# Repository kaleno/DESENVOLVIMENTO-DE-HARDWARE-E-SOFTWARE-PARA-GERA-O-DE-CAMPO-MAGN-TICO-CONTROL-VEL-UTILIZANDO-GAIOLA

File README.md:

# DESENVOLVIMENTO DE HARDWARE E SOFTWARE PARA GERAÇÃO DE CAMPO MAGNÉTICO CONTROLÁVEL

Este repositório contém o trabalho de desenvolvimento de hardware e software realizado no âmbito do Laboratório de Controle e Simulação de Sistemas Aeroespaciais (LODESTAR) da Universidade de Brasília (UnB). O objetivo principal é criar uma plataforma com interface gráfica para a geração de campo magnético controlável, direcionada para aplicações no simulador de pequenos satélites do LODESTAR.

## Visão Geral

O sistema atual do laboratório inclui uma gaiola de Helmholtz com dois pares de bobinas por eixo, uma estação de trabalho e fontes de tensão controláveis. Este projeto propõe atualizações e o desenvolvimento de novas funcionalidades para a plataforma existente.

Algumas das aplicações planejadas são:

- Reprodução do campo magnético em malha fechada utilizando o modelo International Geomagnetic Reference Field (IGRF) em conjunto com o propagador de órbita Simplified General Perturbations (SGP4).
- Reprodução dos vetores de campo magnético coletados pelos sensores do satélite AlfaCrux, recentemente lançado.
- Realização de testes preliminares para validar o novo sistema no contexto dos projetos em andamento no LODESTAR.

## Estrutura do Repositório

O repositório está organizado da seguinte forma:

- `Firmware_Circuito_Inversor/`: Contém os arquivos relacionados ao firmware do circuito inversor.
- `Outros/`: Diretório para outros arquivos relevantes.
- `PonteH/`: Contém os arquivos relacionados à ponte H.
- `PonteH2.0/`: Contém os arquivos relacionados à versão 2.0 da ponte H.
- `Software_Gaiola/`: Contém os arquivos relacionados ao software da gaiola de Helmholtz.
- `Manual_Gaiola_de_Helmholtz_(1).pdf`: Documento PDF contendo o manual da gaiola de Helmholtz.
- `README.md`: Este arquivo README com informações sobre o projeto.
- `TCC_ThiagoHenriqueFerreiradaSilva_biblioteca.pdf`: Documento PDF contendo o TCC (Trabalho de Conclusão de Curso) intitulado "DESENVOLVIMENTO DE HARDWARE E SOFTWARE PARA GERAÇÃO DE CAMPO MAGNÉTICO CONTROLÁVEL".

Certifique-se de ajustar os nomes dos diretórios e arquivos de acordo com a estrutura do seu repositório.

## Pré-requisitos e Instalação

1. Certifique-se de ter os seguintes componentes presentes no arquivo requirements.bat

2. Clone este repositório em sua máquina local usando o seguinte comando:

**git clone https://github.com/seu-usuario/nome-do-repositorio.git**

3. Navegue até o diretório clonado.

4. Siga as instruções específicas contidas em `Manual_Gaiola_de_Helmholtz_(1).pdf` para configurar e instalar as respectivas partes do sistema.

## Utilização

1. Certifique-se de que o hardware está corretamente configurado e conectado à sua estação de trabalho.

2. Inicie o software e abra a interface gráfica do sistema.

3. Utilize as funcionalidades disponíveis para gerar o campo magnético controlável de acordo com suas necessidades.

4. Consulte a documentação disponível em `docs/` para obter informações adicionais sobre a utilização do sistema.

## Contribuição

Se você deseja contribuir para este projeto, sinta-se à vontade para enviar um pull request com suas melhorias. Toda contribuição é bem-vinda!

## Licença

Este projeto é licenciado sob a MIT. Consulte o arquivo LICENSE para obter mais informações.

## Contato

Para mais informações sobre este projeto, entre em contato conosco:

- Nome: Thiago Henrique Ferreira da Silva
- E-mail: thiago.henriquef@hotmail.com

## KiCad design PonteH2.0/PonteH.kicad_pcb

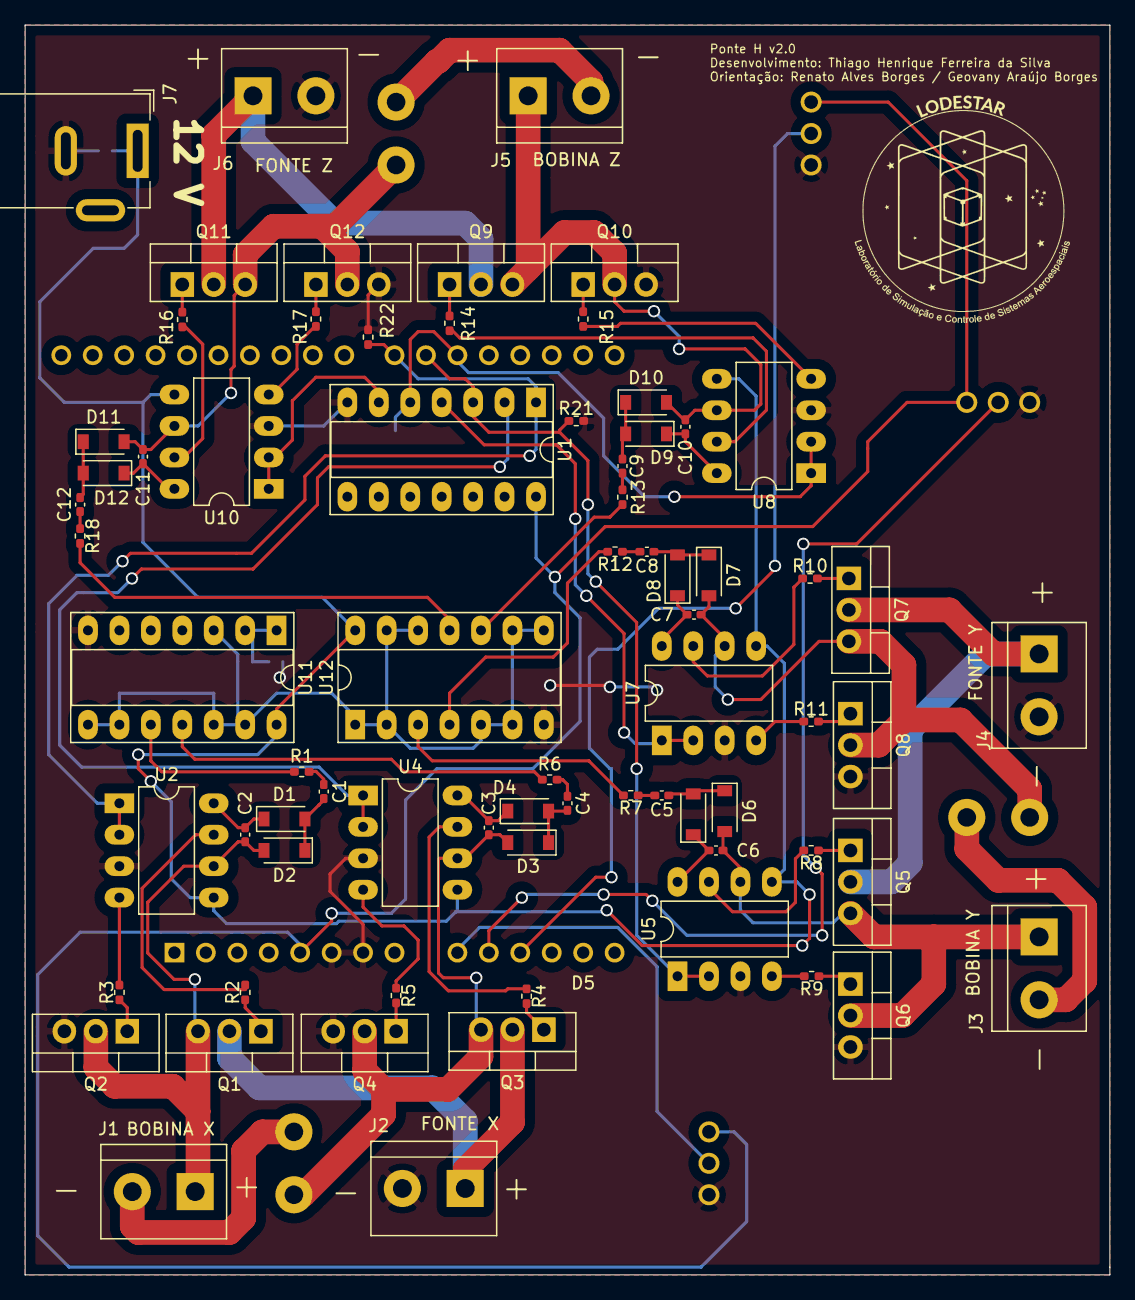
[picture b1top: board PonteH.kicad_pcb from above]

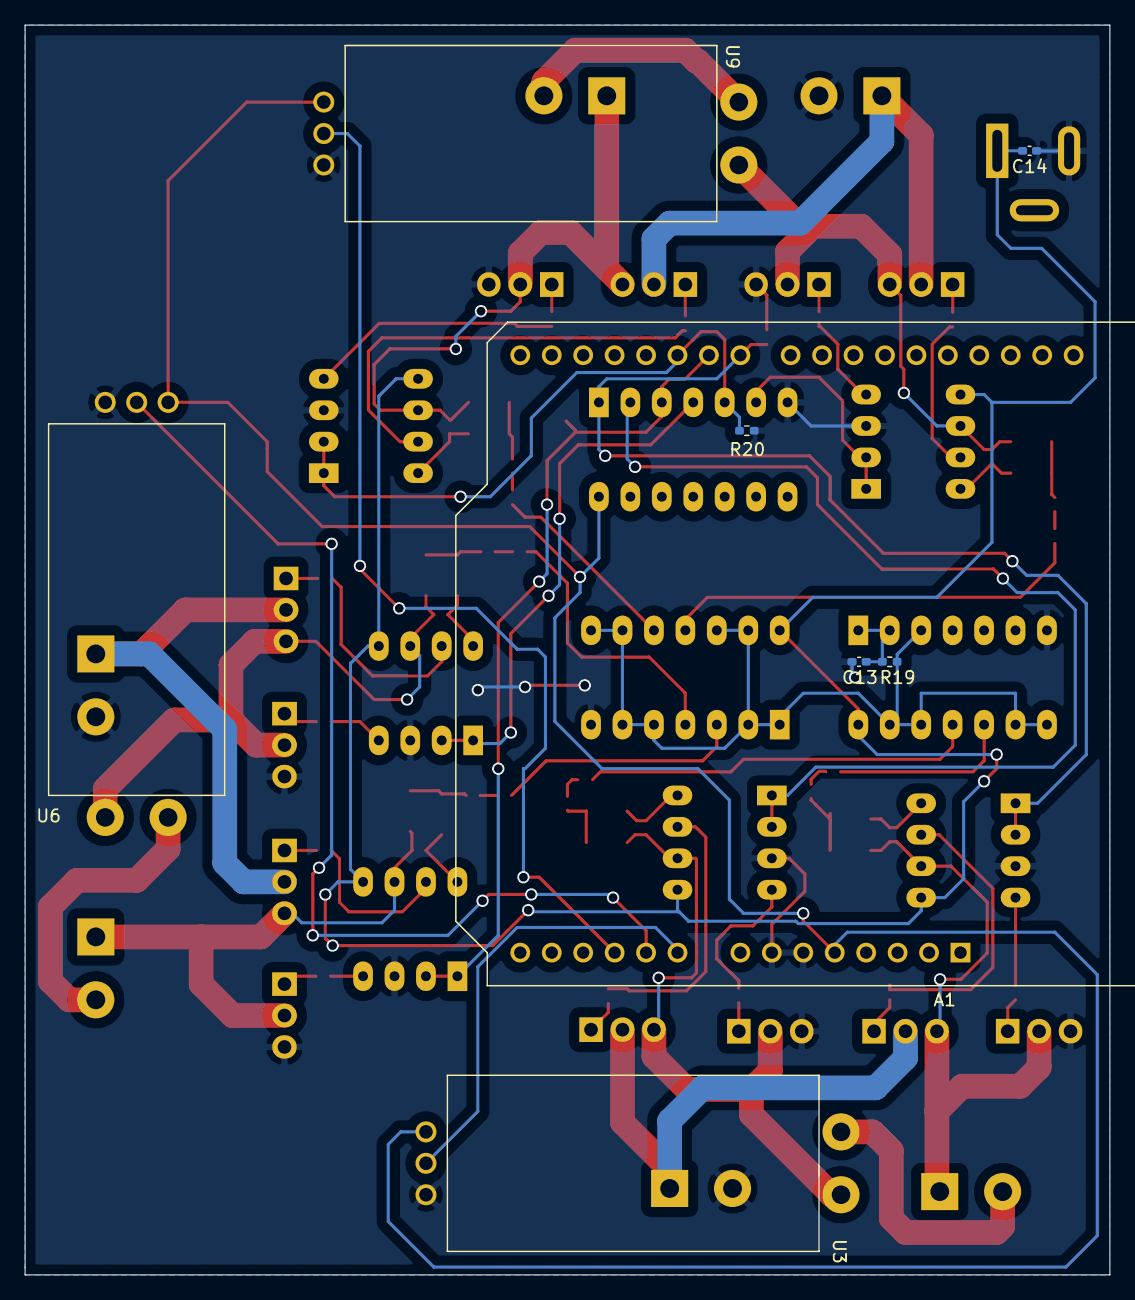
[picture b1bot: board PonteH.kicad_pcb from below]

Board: 2 copper layers, 87.6 x 101.0 mm, 80 parts (8 on the bottom side), 74 nets.

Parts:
A1: Arduino_UNO_R3
C1, C2, C3, C4, C5, C6, C7, C8, C9, C10, C11, C12, C14: 100nF; C_0402_1005Metric_Pad0.74x0.62mm_HandSolder
C13: 1nF; C_0402_1005Metric_Pad0.74x0.62mm_HandSolder
D1, D2, D3, D4, D5, D6, D7, D8, D9, D10, D11, D12: 1N5819; D_SOD-123
J1: Bobinax; TerminalBlock_bornier-2_P5.08mm
J2: Fontex; TerminalBlock_bornier-2_P5.08mm
J3: Bobinay; TerminalBlock_bornier-2_P5.08mm
J4: Fontey; TerminalBlock_bornier-2_P5.08mm
J5: Bobinaz; TerminalBlock_bornier-2_P5.08mm
J6: Fontez; TerminalBlock_bornier-2_P5.08mm
J7: Barrel_Jack_Switch; BarrelJack_Wuerth_6941xx301002
Q1, Q2, Q3, Q4, Q5, Q6, Q7, Q8, Q9, Q10, Q11, Q12: IRFZ44N; TO-220-3_Vertical
R1, R6, R7, R12, R13, R18: 470R; R_0402_1005Metric_Pad0.72x0.64mm_HandSolder
R2, R3, R4, R5, R8, R9, R10, R11, R14, R15, R16, R17: 22R; R_0402_1005Metric_Pad0.72x0.64mm_HandSolder
R19, R20, R21, R22: 12K; R_0402_1005Metric_Pad0.72x0.64mm_HandSolder
U1: 74HC04; DIP-14_W7.62mm_Socket_LongPads
U2, U4, U5, U7, U8, U10: IR2183; DIP-8_W7.62mm_LongPads
U3, U6, U9: ACS715MOD; ACS712
U11, U12: HEF4093B; DIP-14_W7.62mm_Socket_LongPads

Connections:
+5V: A1.5, U1.14, U3.VCC, U6.VCC, U9.VCC
+12V: C14.1, J7.1, U2.5, U4.5, U5.5, U7.5, U8.5, U10.5, U11.14, U12.14
/ArduinoUno/D5: A1.20, R20.1, U1.5, U8.1, U8.2
/ArduinoUno/D6: A1.21, R21.1, U1.3, U5.1, U5.2
/ArduinoUno/D7: A1.22, R22.1, U1.1, U2.1, U2.2
/ArduinoUno/Ix: A1.9, U3.OUT
/ArduinoUno/Iy: A1.10, U6.OUT
/ArduinoUno/Iz: A1.11, U9.OUT
/Ociladores/XA: R1.2, U11.10
/Ociladores/XB: R6.2, U11.11
/Ociladores/YA: R7.2, U12.3
/Ociladores/YB: R12.2, U12.4
/Ociladores/ZA: R13.2, U12.10
/Ociladores/ZB: R18.2, U12.11
/PonteHx/ND7: U1.2, U4.1, U4.2
/PonteHy/ND6: U1.4, U7.1, U7.2
/PonteHz/ND5: U1.6, U10.1, U10.2
GND: A1.6, A1.7, C13.2, C14.2, J2.2, J4.2, J6.2, J7.2, Q2.3, Q4.3, Q6.3, Q8.3, Q10.3, Q12.3, R20.2, R21.2, R22.2, U1.7, U2.3, U3.GND, U4.3, U5.3, U6.GND, U7.3, U8.3, U9.GND, U10.3, U11.7, U12.7
unnamed: C1.1, D1.2, D2.1
unnamed: C1.2, R1.1
unnamed: C2.1, D2.2, J1.1, Q1.3, Q2.2, U2.6
unnamed: C2.2, D1.1, U2.8
unnamed: C3.1, D3.2, Q3.3, Q4.2, U3.I-, U4.6
unnamed: C3.2, D4.1, U4.8
unnamed: C4.1, D3.1, D4.2
unnamed: C4.2, R6.1
unnamed: C5.1, D5.2, D6.1
unnamed: C5.2, R7.1
unnamed: C6.1, D6.2, J3.1, Q5.3, Q6.2, U5.6
unnamed: C6.2, D5.1, U5.8
unnamed: C7.1, D7.2, Q7.3, Q8.2, U6.I-, U7.6
unnamed: C7.2, D8.1, U7.8
unnamed: C8.1, D7.1, D8.2
unnamed: C8.2, R12.1
unnamed: C9.1, D9.2, D10.1
unnamed: C9.2, R13.1
unnamed: C10.1, D10.2, J5.1, Q9.3, Q10.2, U8.6
unnamed: C10.2, D9.1, U8.8
unnamed: C11.1, D11.2, Q11.3, Q12.2, U9.I-, U10.6
unnamed: C11.2, D12.1, U10.8
unnamed: C12.1, D11.1, D12.2
unnamed: C12.2, R18.1
unnamed: C13.1, R19.2, U11.1, U11.2
unnamed: J1.2, U3.I+
unnamed: J2.1, Q1.2, Q3.2
unnamed: J3.2, U6.I+
unnamed: J4.1, Q5.2, Q7.2
unnamed: J5.2, U9.I+
unnamed: J6.1, Q9.2, Q11.2
unnamed: Q1.1, R2.1
unnamed: Q2.1, R3.1
unnamed: Q3.1, R4.2
unnamed: Q4.1, R5.2
unnamed: Q5.1, R8.1
unnamed: Q6.1, R9.1
unnamed: Q7.1, R10.2
unnamed: Q8.1, R11.2
unnamed: Q9.1, R14.1
unnamed: Q10.1, R15.1
unnamed: Q11.1, R16.2
unnamed: Q12.1, R17.2
unnamed: R2.2, U2.7
unnamed: R3.2, U2.4
unnamed: R4.1, U4.7
unnamed: R5.1, U4.4
unnamed: R8.2, U5.7
unnamed: R9.2, U5.4
unnamed: R10.1, U7.7
unnamed: R11.1, U7.4
unnamed: R14.2, U8.7
unnamed: R15.2, U8.4
unnamed: R16.1, U10.7
unnamed: R17.1, U10.4
unnamed: R19.1, U11.3, U11.8, U11.9, U11.12, U11.13, U12.1, U12.2, U12.5, U12.6, U12.8, U12.9, U12.12, U12.13

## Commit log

2023-01-28 Add files via upload
    Versão mais lenta e mais estável
